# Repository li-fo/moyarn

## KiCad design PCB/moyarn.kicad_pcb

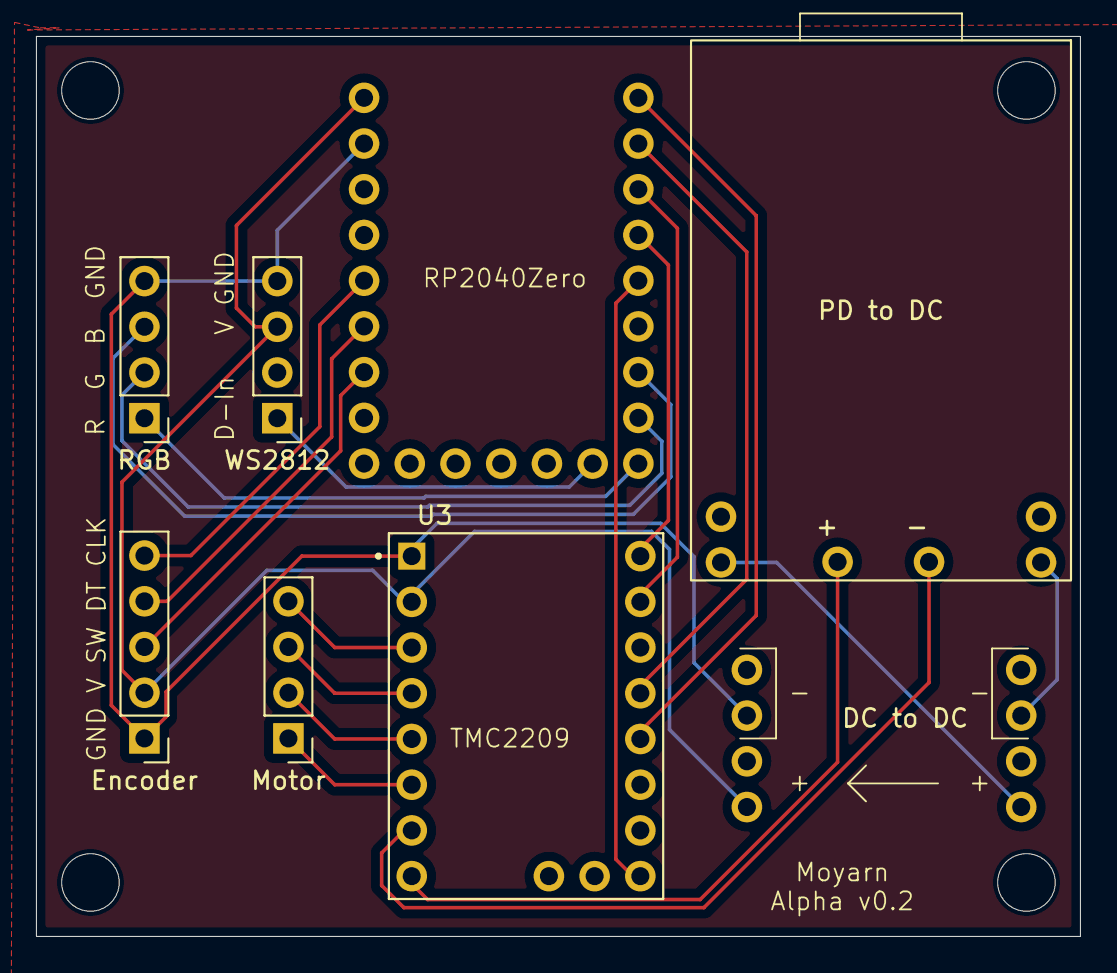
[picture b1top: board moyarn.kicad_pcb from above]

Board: 2 copper layers, 58.0 x 50.0 mm, 12 parts (0 on the bottom side), 22 nets.

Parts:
DC to DC: WeAct_Buck_DCDC; weact-dcdc-footprint-file
Encoder: Conn_01x05_Pin; PinHeader_1x05_P2.54mm_Vertical
H1, H2, H3, H4: MountingHole; MountingHole_3.2mm_M3
Motor: Conn_01x04_Pin; PinHeader_1x04_P2.54mm_Vertical
RGB: Conn_01x04_Pin; PinHeader_1x04_P2.54mm_Vertical
U2: WeAct_USBPD_to_DC; weact-usbpd-to-dc-footprint
U3: TMC2209; TMC2209_SILENTSTEPSTICK_snapeda
U4: rp2040-zero; rp2040-zero-tht_kleeb
WS2812: Conn_01x04_Pin; PinHeader_1x04_P2.54mm_Vertical

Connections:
DIR: U3.9 (DIR), U4.4 (3)
EN: U3.16 (~EN), U4.5 (4)
EN-CLK: Encoder.5, U4.19 (28)
EN-DT: Encoder.4, U4.18 (27)
EN-SW: Encoder.3, U4.17 (26)
LED-B: RGB.3, U4.7 (6)
LED-DIN: U4.10 (9), WS2812.1
LED-G: RGB.2, U4.8 (7)
LED-R: RGB.1, U4.9 (8)
MA1: Motor.2, U3.5 (A1)
MA2: Motor.1, U3.6 (A2)
MB1: Motor.3, U3.4 (B1)
MB2: Motor.4, U3.3 (B2)
MCU5+: DC to DC.1 (VIN+), U2.1 (VOUT+)
MCU5-: DC to DC.3 (VIN-), U2.2 (VOUT-)
MD20+: U2.5 (VOUT+), U3.8 (VM)
MD20-: U2.6 (VOUT-), U3.7 (GND)
RX: U3.12 (RX), U4.2 (1)
STEP: U3.10 (STEP), U4.3 (2)
TX: U3.13 (TX), U4.1 (0)
V5+: DC to DC.8 (VOUT+), Encoder.2, U3.2 (VIO), U4.23 (5V), WS2812.3
V5-: DC to DC.6 (VOUT-), Encoder.1, RGB.4, U3.1 (GND), U4.22 (GND), WS2812.4

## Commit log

2024-06-30 initial....
2024-07-18 change arduino-nano to rp2040-zero
2024-07-26 pcb error mod and source mod
2024-07-26 remove comment
2024-07-26 via pad size change 1.8 to 1.7
2024-08-02 arduino code mod for pcb alpha 02
